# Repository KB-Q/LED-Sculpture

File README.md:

# LED-Sculpture
LED Sculpture is a techno-entertainment project showcased at Envisage show at Shaastra 2020. It involved arranging over 1150 LEDs in a 15ft tall 3D metal frame and displaying cool 3D animations and audio Spectrum patterns (using FFT in MATLAB). Our project has been patented for its unique methods of arranging the LEDs and processing of data for the 3D animations.

## Contents
- LED sculpture report.pdf - design report which documents the mechanical & electronic parts of this project, i.e., shape and size of metal rods, push-pin LED connectors, layout and multiplexing, switching, etc. It also contains explanations for all the code that we used.
- animations.py - python code for generating the data for animations
- FFT_MATLAB.m - MATLAB code for generating audio spectrum patterns using FFT
- arduino_control.ino - Arduino code which sends the signals to the LEDs
- LED_sculpture.brd - Eagle board file of the PCB design
- LED_sculpture.sch - Eagle schematic of the PCB design

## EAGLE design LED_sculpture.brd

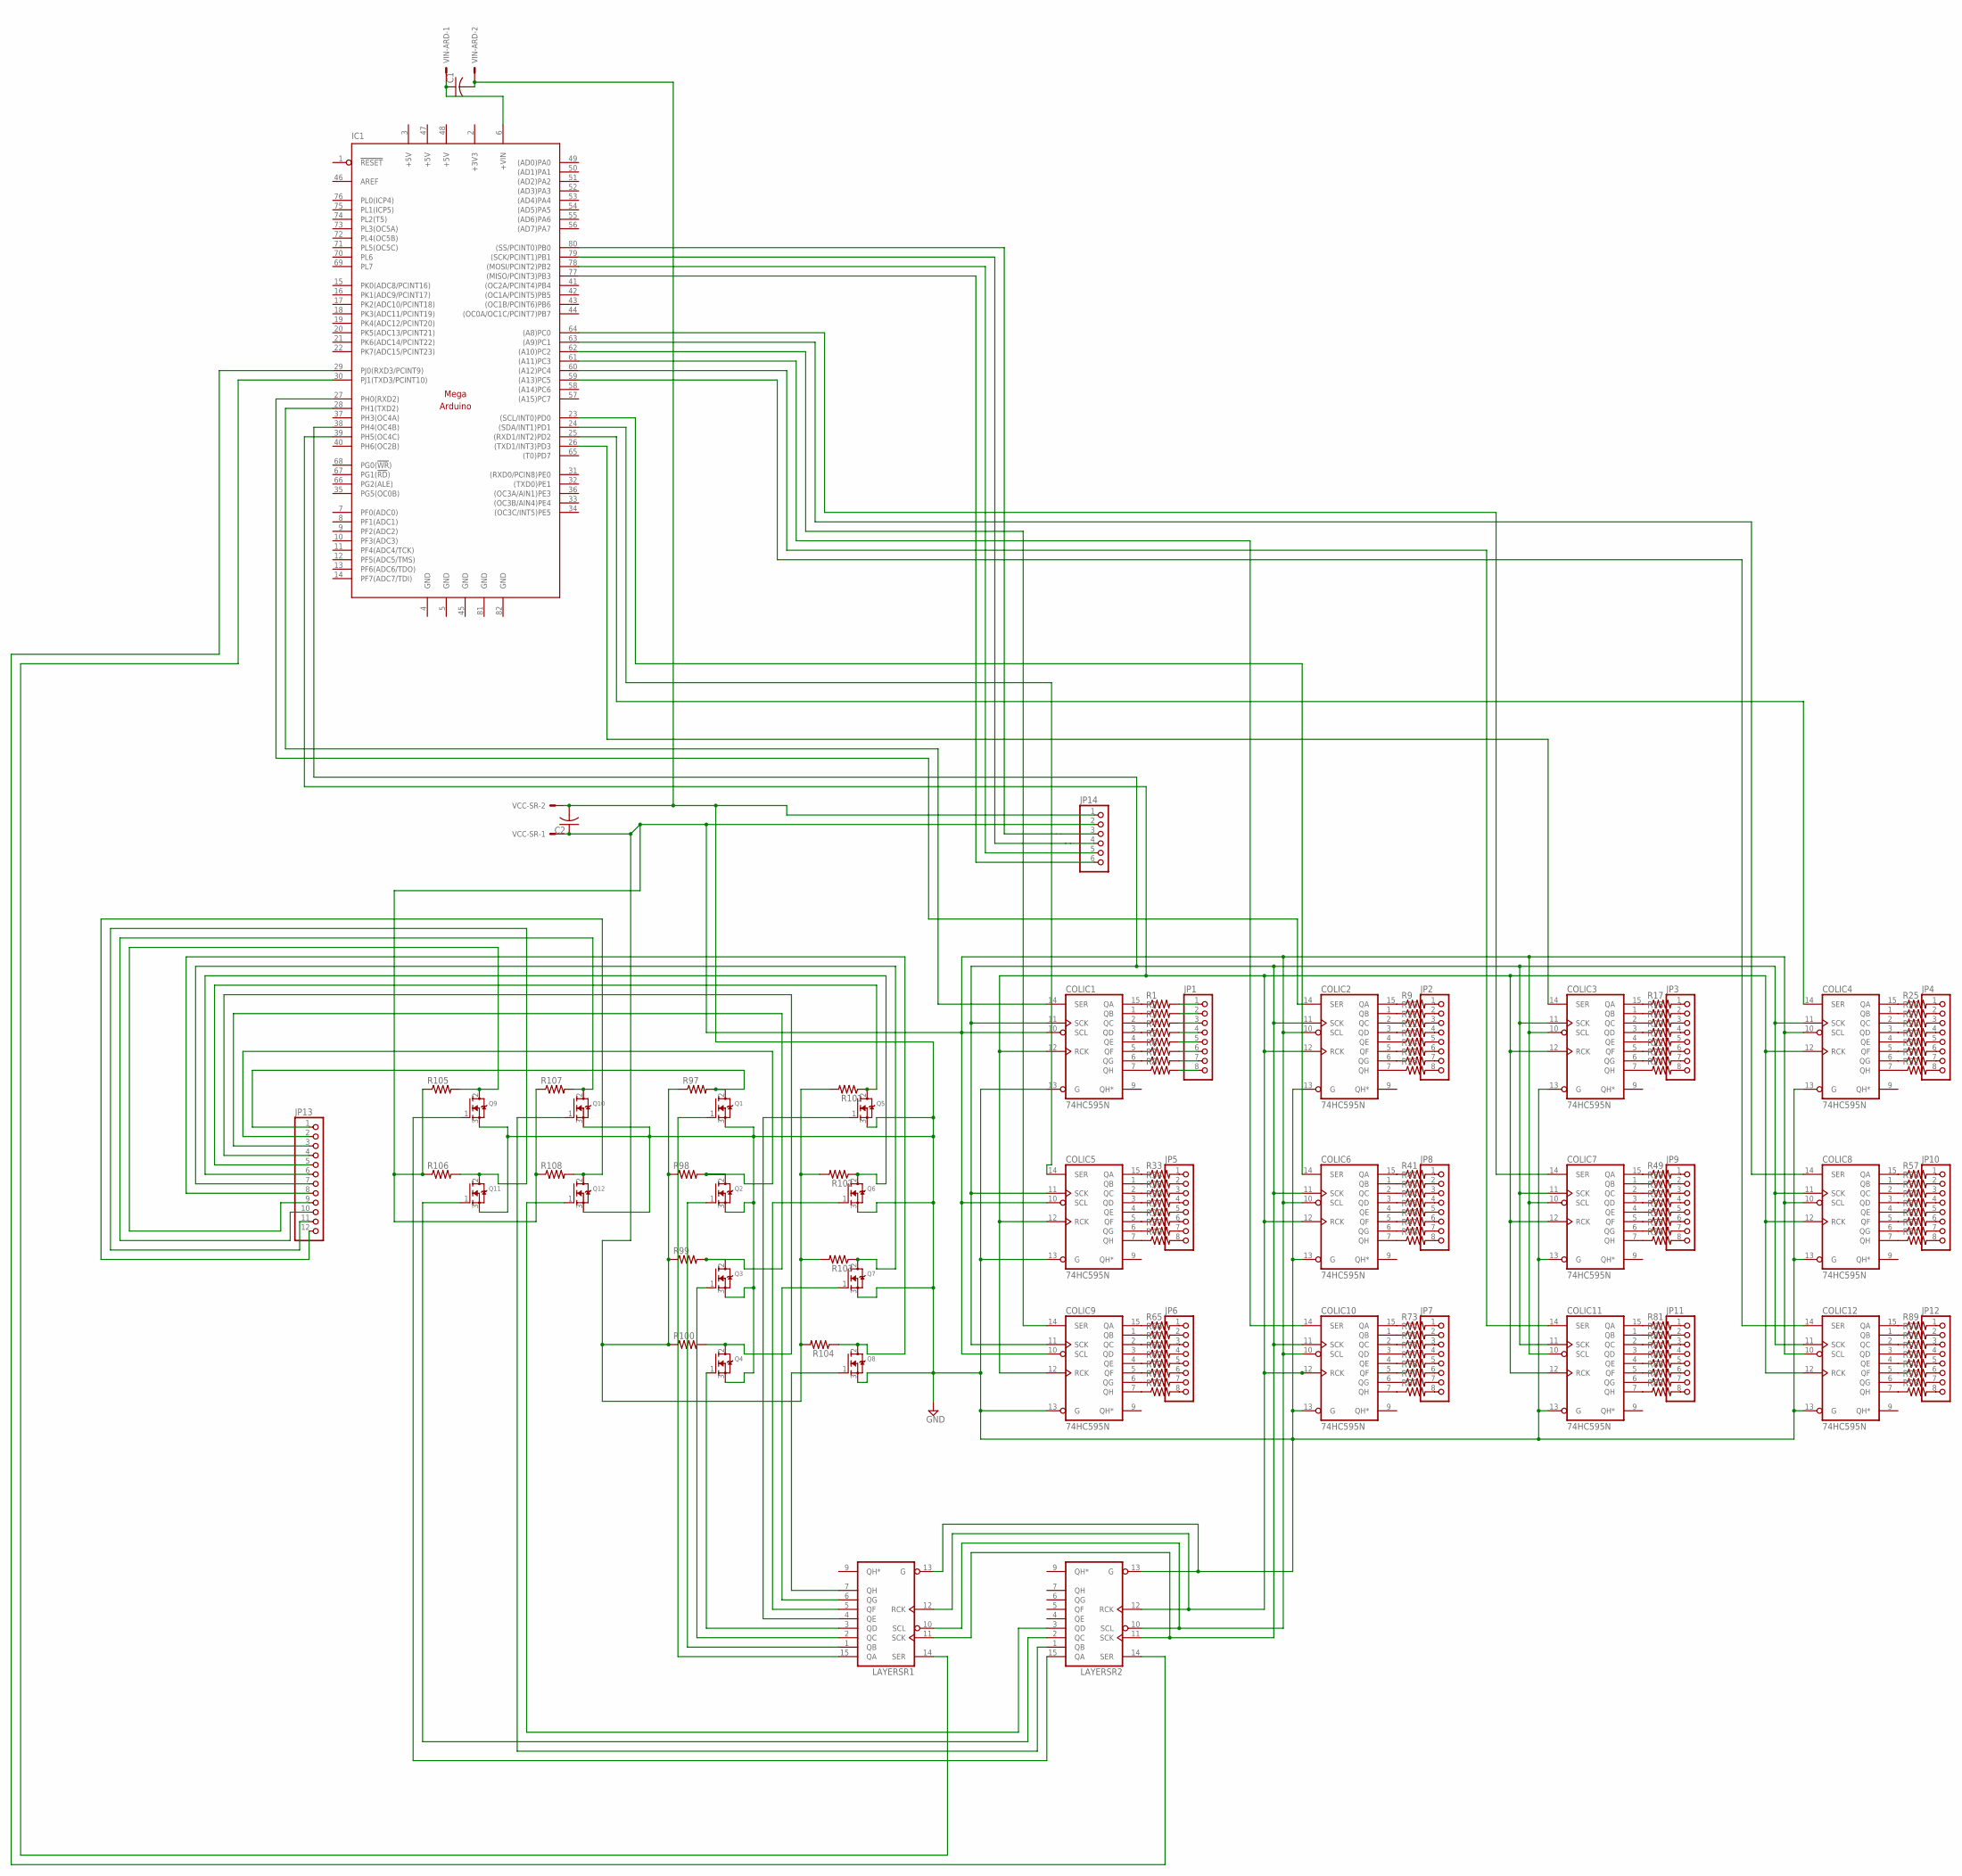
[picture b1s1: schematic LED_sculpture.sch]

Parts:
C1, C2: C-US025-025X050; C025-025X050
COLIC1, COLIC2, COLIC3, COLIC4, COLIC5, COLIC6, COLIC7, COLIC8, COLIC9, COLIC10, COLIC11, COLIC12: 74HC595N; DIL16
IC1: MEGAARDUINO_1; MEGA_ARDUINO
JP1, JP2, JP3, JP4, JP5, JP6, JP7, JP8, JP9, JP10, JP11, JP12: PINHD-1X8CLEANBIG; 1X08-CLEANBIG
JP13: PINHD-1X12; 1X12
JP14: PINHD-1X6; 1X06
LAYERSR1, LAYERSR2: 74HC595N; DIL16
Q1, Q2, Q3, Q4, Q5, Q6, Q7, Q8, Q9, Q10, Q11, Q12: MOSFET-NGDS_TO220V; TO220V
R1, R2, R3, R4, R5, R6, R7, R8, R9, R10, R11, R12, R13, R14, R15, R16, R17, R18, R19, R20, R21, R22, R23, R24, R25, R26, R27, R28, R29, R30, R31, R32, R33, R34, R35, R36, R37, R38, R39, R40, R41, R42, R43, R44, R45, R46, R47, R48, R49, R50, R51, R52, R53, R54, R55, R56, R57, R58, R59, R60, R61, R62, R63, R64, R65, R66, R67, R68, R69, R70, R71, R72, R73, R74, R75, R76, R77, R78, R79, R80, R81, R82, R83, R84, R85, R86, R87, R88, R89, R90, R91, R92, R93, R94, R95, R96, R97, R98, R99, R100, R101, R102, R103, R104, R105, R106, R107, R108: R-US_0204/7; 0204/7
VCC-SR: KK-156-2
VIN-ARD: KK-156-2

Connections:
5V: C2.1, COLIC1.10 (SCL), COLIC2.10 (SCL), COLIC3.10 (SCL), COLIC4.10 (SCL), COLIC5.10 (SCL), COLIC6.10 (SCL), COLIC7.10 (SCL), COLIC8.10 (SCL), COLIC9.10 (SCL), COLIC10.10 (SCL), COLIC11.10 (SCL), COLIC12.10 (SCL), JP14.2, LAYERSR1.10 (SCL), LAYERSR2.10 (SCL), R97.1, R98.1, R99.1, R100.1, R101.2, R102.2, R103.2, R104.2, R105.1, R106.1, R107.1, R108.1, VCC-SR.1
+3V3: IC1.2 (+3V3)
+5V: IC1.3 (+5V), IC1.47 (+5V), IC1.48 (+5V)
GND: C1.2, C2.2, COLIC1.8 (GND), COLIC1.13 (G), COLIC2.8 (GND), COLIC2.13 (G), COLIC3.8 (GND), COLIC3.13 (G), COLIC4.8 (GND), COLIC4.13 (G), COLIC5.8 (GND), COLIC5.13 (G), COLIC6.8 (GND), COLIC6.13 (G), COLIC7.8 (GND), COLIC7.13 (G), COLIC8.8 (GND), COLIC8.13 (G), COLIC9.8 (GND), COLIC9.13 (G), COLIC10.8 (GND), COLIC10.13 (G), COLIC11.8 (GND), COLIC11.13 (G), COLIC12.8 (GND), COLIC12.13 (G), IC1.4 (GND), IC1.5 (GND), IC1.45 (GND), IC1.81 (GND), IC1.82 (GND), JP14.1, LAYERSR1.8 (GND), LAYERSR1.13 (G), LAYERSR2.8 (GND), LAYERSR2.13 (G), Q1.3 (S), Q2.3 (S), Q3.3 (S), Q4.3 (S), Q5.3 (S), Q6.3 (S), Q7.3 (S), Q8.3 (S), Q9.3 (S), Q10.3 (S), Q11.3 (S), Q12.3 (S), VCC-SR.2, VIN-ARD.2
unnamed: LAYERSR1.7 (QH), Q8.1 (G)
unnamed: LAYERSR1.6 (QG), Q7.1 (G)
unnamed: LAYERSR1.5 (QF), Q6.1 (G)
unnamed: LAYERSR1.4 (QE), Q5.1 (G)
unnamed: LAYERSR1.3 (QD), Q4.1 (G)
unnamed: LAYERSR1.2 (QC), Q3.1 (G)
unnamed: JP13.1, Q1.2 (D), R97.2
unnamed: LAYERSR1.15 (QA), Q1.1 (G)
unnamed: LAYERSR2.3 (QD), Q12.1 (G)
unnamed: JP13.5, Q5.2 (D), R101.1
unnamed: JP13.3, Q3.2 (D), R99.2
unnamed: JP13.6, Q6.2 (D), R102.1
unnamed: IC1.78 ((MOSI/PCINT2)PB2), JP14.5
unnamed: JP13.2, Q2.2 (D), R98.2
unnamed: IC1.77 ((MISO/PCINT3)PB3), JP14.6
unnamed: JP13.4, Q4.2 (D), R100.2
unnamed: IC1.79 ((SCK/PCINT1)PB1), JP14.4
unnamed: LAYERSR2.2 (QC), Q11.1 (G)
unnamed: IC1.80 ((SS/PCINT0)PB0), JP14.3
unnamed: LAYERSR2.15 (QA), Q9.1 (G)
unnamed: COLIC7.14 (SER), IC1.64 ((A8)PC0)
unnamed: JP13.7, Q7.2 (D), R103.1
unnamed: COLIC9.14 (SER), IC1.62 ((A10)PC2)
unnamed: JP13.8, Q8.2 (D), R104.1
unnamed: JP13.9, Q9.2 (D), R105.2
unnamed: JP13.10, Q10.2 (D), R107.2
unnamed: JP13.11, Q11.2 (D), R106.2
unnamed: JP13.12, Q12.2 (D), R108.2
unnamed: COLIC8.14 (SER), IC1.63 ((A9)PC1)
unnamed: IC1.30 (PJ1(TXD3/PCINT10)), LAYERSR1.14 (SER)
unnamed: COLIC2.15 (QA), R9.1
unnamed: COLIC1.15 (QA), R1.1
unnamed: COLIC1.1 (QB), R2.1
unnamed: COLIC1.2 (QC), R3.1
unnamed: COLIC1.3 (QD), R4.1
unnamed: COLIC1.4 (QE), R5.1
unnamed: COLIC1.5 (QF), R6.1
unnamed: COLIC1.6 (QG), R7.1
unnamed: COLIC1.7 (QH), R8.1
unnamed: COLIC2.1 (QB), R10.1
unnamed: COLIC2.2 (QC), R11.1
unnamed: COLIC2.3 (QD), R12.1
unnamed: COLIC2.4 (QE), R13.1
unnamed: COLIC2.5 (QF), R14.1
unnamed: COLIC2.6 (QG), R15.1
unnamed: COLIC2.7 (QH), R16.1
unnamed: COLIC3.15 (QA), R17.1
unnamed: COLIC3.1 (QB), R18.1
unnamed: COLIC3.2 (QC), R19.1
unnamed: COLIC3.3 (QD), R20.1
unnamed: COLIC3.4 (QE), R21.1
unnamed: COLIC3.5 (QF), R22.1
unnamed: COLIC3.6 (QG), R23.1
unnamed: COLIC3.7 (QH), R24.1
unnamed: COLIC4.15 (QA), R25.1
unnamed: COLIC4.1 (QB), R26.1
unnamed: COLIC4.2 (QC), R27.1
unnamed: COLIC4.3 (QD), R28.1
unnamed: COLIC4.4 (QE), R29.1
unnamed: COLIC4.5 (QF), R30.1
unnamed: COLIC4.6 (QG), R31.1
unnamed: COLIC4.7 (QH), R32.1
unnamed: COLIC5.15 (QA), R33.1
unnamed: COLIC5.1 (QB), R34.1
unnamed: COLIC5.2 (QC), R35.1
unnamed: COLIC5.3 (QD), R36.1
unnamed: COLIC5.4 (QE), R37.1
unnamed: COLIC5.5 (QF), R38.1
unnamed: COLIC5.6 (QG), R39.1
unnamed: COLIC5.7 (QH), R40.1
unnamed: COLIC6.15 (QA), R41.1
unnamed: COLIC6.1 (QB), R42.1
unnamed: COLIC6.2 (QC), R43.1
unnamed: COLIC6.3 (QD), R44.1
unnamed: COLIC6.4 (QE), R45.1
unnamed: COLIC6.5 (QF), R46.1
unnamed: COLIC6.6 (QG), R47.1
unnamed: COLIC6.7 (QH), R48.1
unnamed: COLIC7.15 (QA), R49.1
unnamed: COLIC7.1 (QB), R50.1
unnamed: COLIC7.2 (QC), R51.1
unnamed: COLIC7.3 (QD), R52.1
unnamed: COLIC7.4 (QE), R53.1
unnamed: COLIC7.5 (QF), R54.1
unnamed: COLIC7.6 (QG), R55.1
unnamed: COLIC7.7 (QH), R56.1
unnamed: COLIC8.15 (QA), R57.1
unnamed: COLIC8.1 (QB), R58.1
unnamed: COLIC8.2 (QC), R59.1
unnamed: COLIC8.3 (QD), R60.1
unnamed: COLIC8.4 (QE), R61.1
unnamed: COLIC8.5 (QF), R62.1
unnamed: COLIC8.6 (QG), R63.1
unnamed: COLIC8.7 (QH), R64.1
unnamed: COLIC9.15 (QA), R65.1
unnamed: COLIC9.1 (QB), R66.1
unnamed: COLIC9.2 (QC), R67.1
unnamed: COLIC9.3 (QD), R68.1
unnamed: COLIC9.4 (QE), R69.1
unnamed: COLIC9.5 (QF), R70.1
unnamed: COLIC9.6 (QG), R71.1
unnamed: COLIC9.7 (QH), R72.1
unnamed: COLIC10.15 (QA), R73.1
unnamed: COLIC10.1 (QB), R74.1
unnamed: COLIC10.2 (QC), R75.1
unnamed: COLIC10.3 (QD), R76.1
unnamed: COLIC10.4 (QE), R77.1
unnamed: COLIC10.5 (QF), R78.1
unnamed: COLIC10.6 (QG), R79.1
unnamed: COLIC10.7 (QH), R80.1
unnamed: COLIC11.15 (QA), R81.1
unnamed: COLIC11.1 (QB), R82.1
unnamed: COLIC11.2 (QC), R83.1
unnamed: COLIC11.3 (QD), R84.1
unnamed: COLIC11.4 (QE), R85.1
unnamed: COLIC11.5 (QF), R86.1
unnamed: COLIC11.6 (QG), R87.1
unnamed: COLIC11.7 (QH), R88.1
unnamed: COLIC12.15 (QA), R89.1
unnamed: COLIC12.1 (QB), R90.1
unnamed: COLIC12.2 (QC), R91.1
unnamed: COLIC12.3 (QD), R92.1
unnamed: COLIC12.4 (QE), R93.1
unnamed: COLIC12.5 (QF), R94.1
unnamed: COLIC12.6 (QG), R95.1
unnamed: COLIC12.7 (QH), R96.1
unnamed: JP1.1, R1.2
unnamed: JP1.2, R2.2
unnamed: JP1.3, R3.2
unnamed: JP1.4, R4.2
unnamed: JP1.5, R5.2
unnamed: JP1.6, R6.2
unnamed: JP1.7, R7.2
unnamed: JP1.8, R8.2
unnamed: JP2.1, R9.2
unnamed: JP2.2, R10.2
unnamed: JP2.3, R11.2
unnamed: JP2.4, R12.2
unnamed: JP2.5, R13.2
unnamed: JP2.6, R14.2
unnamed: JP2.7, R15.2
unnamed: JP2.8, R16.2
unnamed: JP3.1, R17.2
unnamed: JP3.2, R18.2
unnamed: JP3.3, R19.2
unnamed: JP3.4, R20.2
unnamed: JP3.5, R21.2
unnamed: JP3.6, R22.2
unnamed: JP3.7, R23.2
unnamed: JP3.8, R24.2
unnamed: JP4.1, R25.2
unnamed: JP4.2, R26.2
unnamed: JP4.3, R27.2
unnamed: JP4.4, R28.2
unnamed: JP4.5, R29.2
unnamed: JP4.6, R30.2
unnamed: JP4.7, R31.2
unnamed: JP4.8, R32.2
unnamed: JP5.1, R33.2
unnamed: JP5.2, R34.2
unnamed: JP5.3, R35.2
unnamed: JP5.4, R36.2
unnamed: JP5.5, R37.2
unnamed: JP5.6, R38.2
unnamed: JP5.7, R39.2
unnamed: JP5.8, R40.2
unnamed: JP6.1, R65.2
unnamed: JP6.2, R66.2
unnamed: JP6.3, R67.2
unnamed: JP6.4, R68.2
unnamed: JP6.5, R69.2
unnamed: JP6.6, R70.2
unnamed: JP6.7, R71.2
unnamed: JP6.8, R72.2
unnamed: JP7.1, R73.2
unnamed: JP7.2, R74.2
unnamed: JP7.3, R75.2
unnamed: JP7.4, R76.2
unnamed: JP7.5, R77.2
unnamed: JP7.6, R78.2
unnamed: JP7.7, R79.2
unnamed: JP7.8, R80.2
unnamed: JP8.1, R41.2
unnamed: JP8.2, R42.2
unnamed: JP8.3, R43.2
unnamed: JP8.4, R44.2
unnamed: JP8.5, R45.2
unnamed: JP8.6, R46.2
unnamed: JP8.7, R47.2
unnamed: JP8.8, R48.2
unnamed: JP9.1, R49.2
unnamed: JP9.2, R50.2
unnamed: JP9.3, R51.2
unnamed: JP9.4, R52.2
unnamed: JP9.5, R53.2
unnamed: JP9.6, R54.2
unnamed: JP9.7, R55.2
unnamed: JP9.8, R56.2
unnamed: JP10.1, R57.2
unnamed: JP10.2, R58.2
unnamed: JP10.3, R59.2
unnamed: JP10.4, R60.2
unnamed: JP10.5, R61.2
unnamed: JP10.6, R62.2
unnamed: JP10.7, R63.2
unnamed: JP10.8, R64.2
unnamed: JP11.1, R81.2
unnamed: JP11.2, R82.2
unnamed: JP11.3, R83.2
unnamed: JP11.4, R84.2
unnamed: JP11.5, R85.2
unnamed: JP11.6, R86.2
unnamed: JP11.7, R87.2
unnamed: JP11.8, R88.2
unnamed: JP12.1, R89.2
unnamed: JP12.2, R90.2
unnamed: JP12.3, R91.2
unnamed: JP12.4, R92.2
unnamed: JP12.5, R93.2
unnamed: JP12.6, R94.2
unnamed: JP12.7, R95.2
unnamed: JP12.8, R96.2
unnamed: COLIC10.14 (SER), IC1.61 ((A11)PC3)
unnamed: COLIC11.14 (SER), IC1.60 ((A12)PC4)
unnamed: COLIC12.14 (SER), IC1.59 ((A13)PC5)
unnamed: LAYERSR2.1 (QB), Q10.1 (G)
unnamed: IC1.29 (PJ0(RXD3/PCINT9)), LAYERSR2.14 (SER)
unnamed: COLIC1.14 (SER), IC1.28 (PH1(TXD2))
unnamed: COLIC2.14 (SER), IC1.27 (PH0(RXD2))
unnamed: COLIC3.14 (SER), IC1.26 ((TXD1/INT3)PD3)
unnamed: COLIC4.14 (SER), IC1.25 ((RXD1/INT2)PD2)
unnamed: COLIC1.12 (RCK), COLIC2.12 (RCK), COLIC3.12 (RCK), COLIC4.12 (RCK), COLIC5.12 (RCK), COLIC6.12 (RCK), COLIC7.12 (RCK), COLIC8.12 (RCK), COLIC9.12 (RCK), COLIC10.12 (RCK), COLIC11.12 (RCK), COLIC12.12 (RCK), IC1.39 (PH5(OC4C)), LAYERSR1.12 (RCK), LAYERSR2.12 (RCK)
unnamed: COLIC5.14 (SER), IC1.24 ((SDA/INT1)PD1)
unnamed: COLIC1.11 (SCK), COLIC2.11 (SCK), COLIC3.11 (SCK), COLIC4.11 (SCK), COLIC5.11 (SCK), COLIC6.11 (SCK), COLIC7.11 (SCK), COLIC8.11 (SCK), COLIC9.11 (SCK), COLIC10.11 (SCK), COLIC11.11 (SCK), COLIC12.11 (SCK), IC1.38 (PH4(OC4B)), LAYERSR1.11 (SCK), LAYERSR2.11 (SCK)
unnamed: COLIC6.14 (SER), IC1.23 ((SCL/INT0)PD0)
Q3: LAYERSR1.1 (QB), Q2.1 (G)
VCC: COLIC1.16 (VCC), COLIC2.16 (VCC), COLIC3.16 (VCC), COLIC4.16 (VCC), COLIC5.16 (VCC), COLIC6.16 (VCC), COLIC7.16 (VCC), COLIC8.16 (VCC), COLIC9.16 (VCC), COLIC10.16 (VCC), COLIC11.16 (VCC), COLIC12.16 (VCC), LAYERSR1.16 (VCC), LAYERSR2.16 (VCC)
VIN: C1.1, IC1.6 (+VIN), VIN-ARD.1

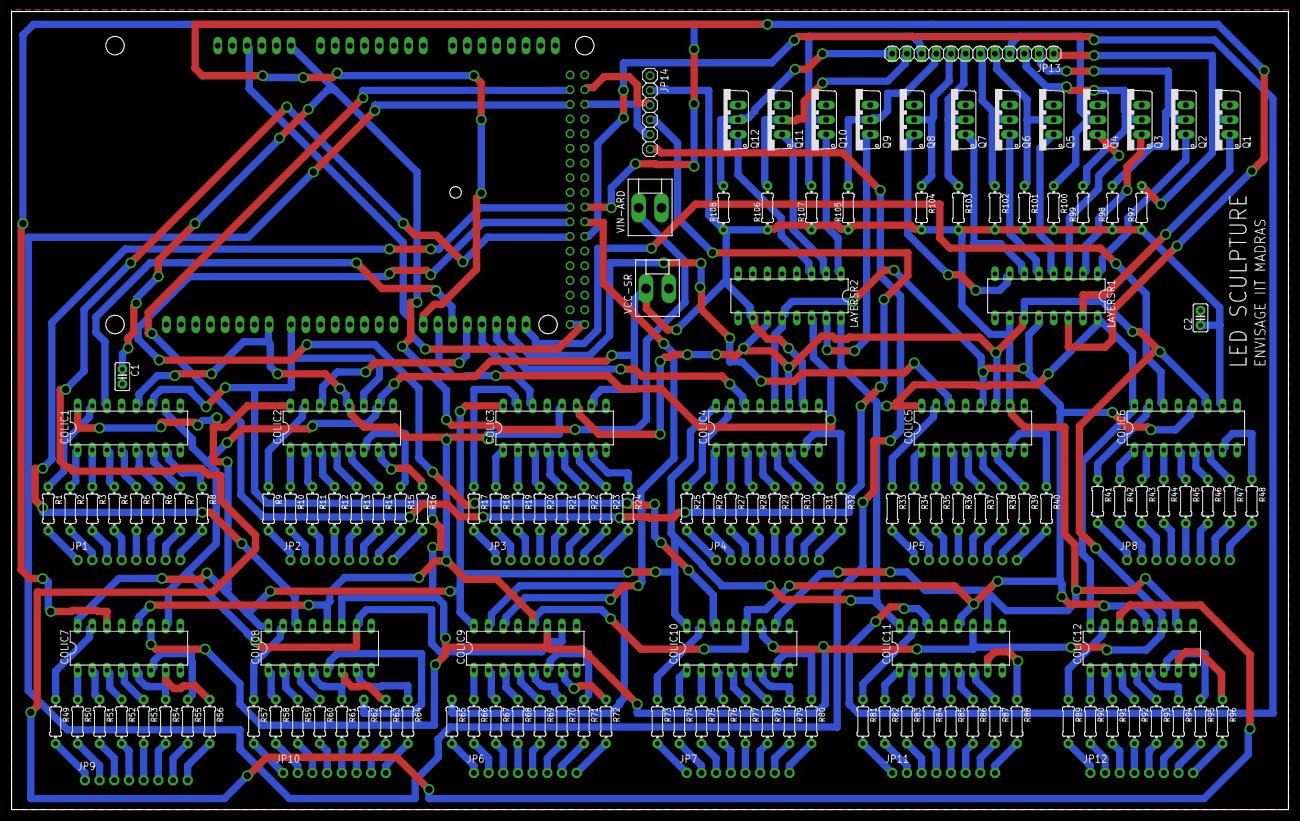
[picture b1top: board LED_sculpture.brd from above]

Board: 2 copper layers, 221.0 x 138.1 mm, 153 parts (1 on the bottom side), 241 nets.

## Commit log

2020-06-24 Create Arduino_control
2020-06-24 Rename FFT_MATLAB.m to FFT_MATLAB
2020-06-24 Rename FFT_MATLAB to FFT_MATLAB.m
2020-06-24 Rename Arduino_control to arduino_control.ino
